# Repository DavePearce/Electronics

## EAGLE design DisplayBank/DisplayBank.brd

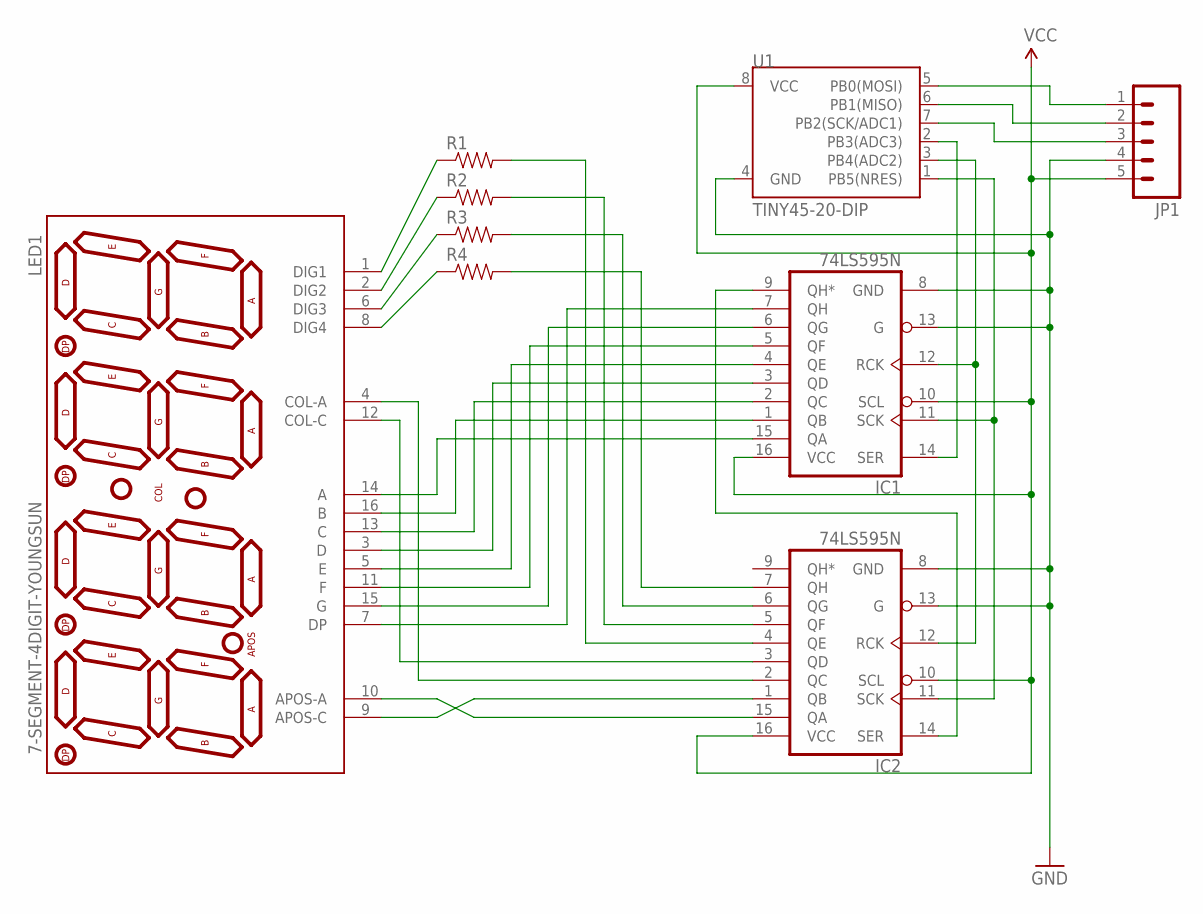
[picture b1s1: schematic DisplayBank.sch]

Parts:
IC1, IC2: 74LS595N; DIL16
JP1: M05NO_SILK; 1X05_NO_SILK
LED1: 7-SEGMENT-4DIGIT-YOUNGSUN
R1, R2, R3, R4: RESISTORPTH-1/4W; AXIAL-0.4
U1: TINY45-20-DIP; DIP08

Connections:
GND: IC1.8 (GND), IC1.13 (G), IC2.8 (GND), IC2.13 (G), JP1.4, U1.4 (GND)
unnamed: IC1.2 (QC), LED1.13 (C)
unnamed: IC1.3 (QD), LED1.3 (D)
unnamed: IC1.15 (QA), LED1.14 (A)
unnamed: IC1.1 (QB), LED1.16 (B)
unnamed: IC1.4 (QE), LED1.5 (E)
unnamed: IC1.5 (QF), LED1.11 (F)
unnamed: IC1.6 (QG), LED1.15 (G)
unnamed: IC1.7 (QH), LED1.7 (DP)
unnamed: IC1.9 (QH*), IC2.14 (SER)
unnamed: LED1.8 (DIG4), R4.P$1 (1)
unnamed: LED1.6 (DIG3), R3.P$1 (1)
unnamed: LED1.2 (DIG2), R2.P$1 (1)
unnamed: LED1.1 (DIG1), R1.P$1 (1)
unnamed: IC2.15 (QA), LED1.10 (APOS-A)
unnamed: IC2.1 (QB), LED1.9 (APOS-C)
unnamed: IC2.2 (QC), LED1.4 (COL-A)
unnamed: IC2.3 (QD), LED1.12 (COL-C)
unnamed: IC2.4 (QE), R1.P$2 (2)
unnamed: IC2.5 (QF), R2.P$2 (2)
unnamed: IC2.6 (QG), R3.P$2 (2)
unnamed: IC2.7 (QH), R4.P$2 (2)
unnamed: IC1.12 (RCK), IC2.12 (RCK), U1.3 (PB4(ADC2))
unnamed: IC1.11 (SCK), IC2.11 (SCK), U1.1 (PB5(NRES))
unnamed: JP1.1, U1.5 (PB0(MOSI))
unnamed: JP1.2, U1.6 (PB1(MISO))
unnamed: JP1.3, U1.7 (PB2(SCK/ADC1))
unnamed: IC1.14 (SER), U1.2 (PB3(ADC3))
VCC: IC1.10 (SCL), IC1.16 (VCC), IC2.10 (SCL), IC2.16 (VCC), JP1.5, U1.8 (VCC)

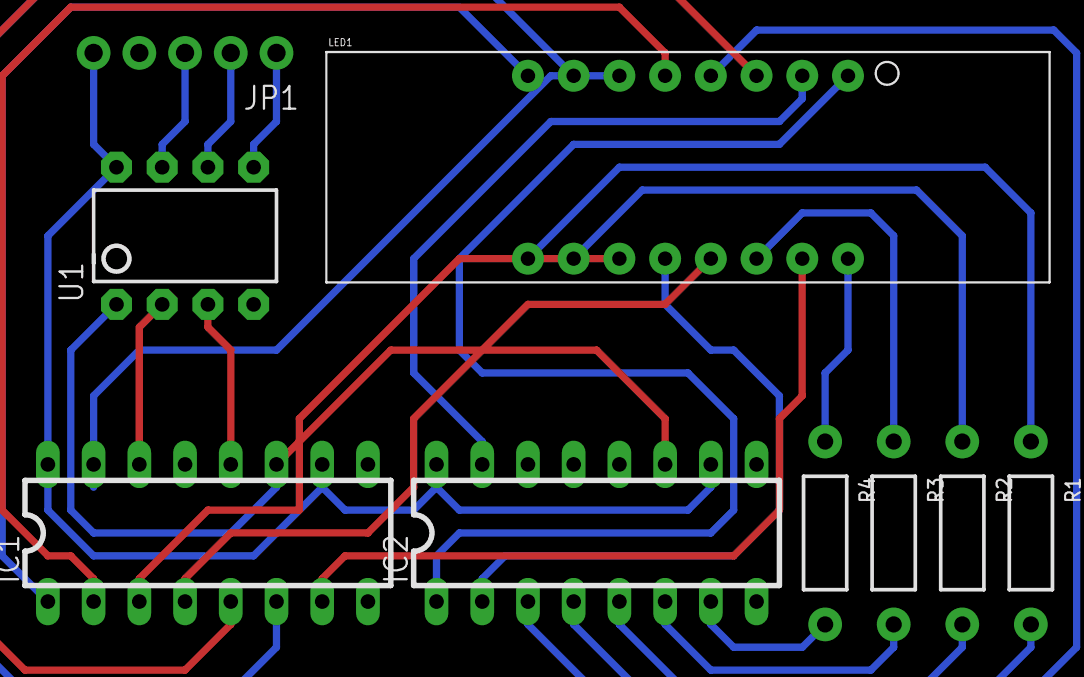
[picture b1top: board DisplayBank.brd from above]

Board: 2 copper layers, 9 parts (0 on the bottom side), 29 nets.

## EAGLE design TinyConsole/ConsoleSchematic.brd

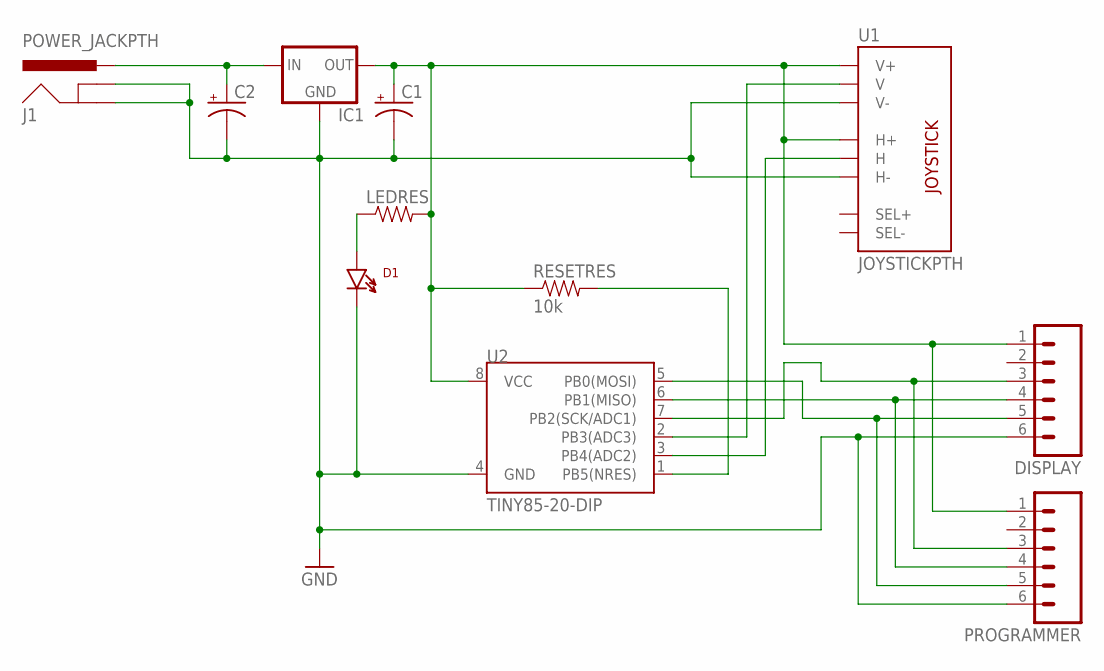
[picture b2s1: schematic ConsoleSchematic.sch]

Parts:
C1, C2: 10UF-25V-20%(PTH)KIT; CPOL-RADIAL-10UF-25V-KIT
D1: LTE-302
DISPLAY: M06SILK_FEMALE_PTH; 1X06
IC1: V_REG_78XXSIDE; 78XXL
J1: POWER_JACKPTH; POWER_JACK_PTH
LEDRES: RESISTOREZ; AXIAL-0.3EZ
PROGRAMMER: M06SILK_FEMALE_PTH; 1X06
RESETRES: 10k; AXIAL-0.3
U1: JOYSTICKPTH; JOYSTICK
U2: TINY85-20-DIP; DIP08

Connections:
CS: DISPLAY.4, PROGRAMMER.4, U2.6 (PB1(MISO))
GND: C1.2 (-), C2.2 (-), D1.C, DISPLAY.6, IC1.GND, J1.GND, J1.GNDBREAK, PROGRAMMER.6, U1.H3 (H-), U1.V3 (V-), U2.4 (GND)
MOSI: DISPLAY.5, PROGRAMMER.5, U2.5 (PB0(MOSI))
unnamed: D1.A, LEDRES.P$1 (1)
unnamed: RESETRES.P$2 (2), U2.1 (PB5(NRES))
unnamed: U1.V2 (V), U2.2 (PB3(ADC3))
unnamed: U1.H2 (H), U2.3 (PB4(ADC2))
unnamed: C2.1 (+), IC1.IN, J1.PWR
SCK: DISPLAY.3, PROGRAMMER.3, U2.7 (PB2(SCK/ADC1))
VCC: C1.1 (+), DISPLAY.1, IC1.OUT, LEDRES.P$2 (2), PROGRAMMER.1, RESETRES.P$1 (1), U1.H1 (H+), U1.V1 (V+), U2.8 (VCC)

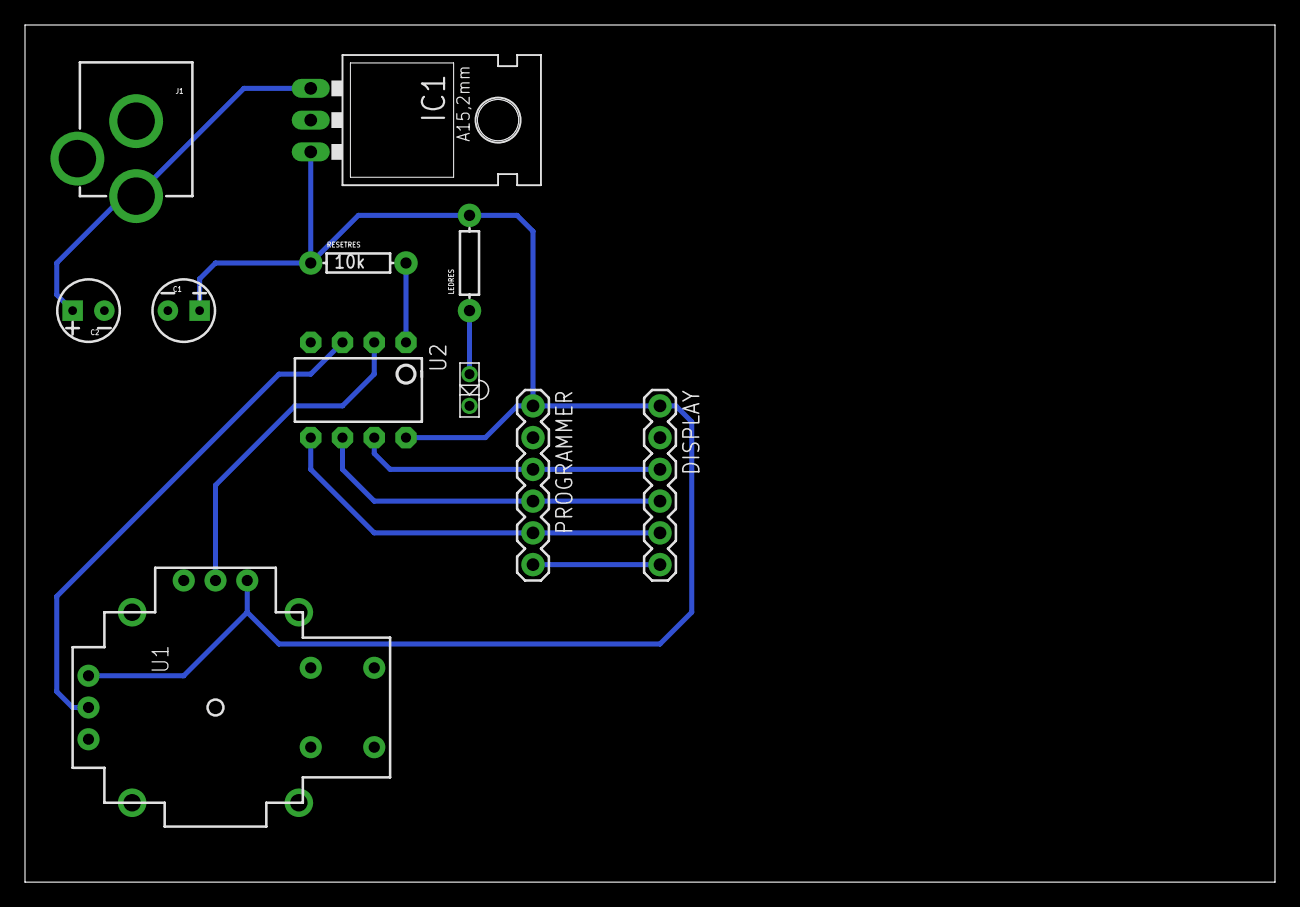
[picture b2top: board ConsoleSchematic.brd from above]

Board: 2 copper layers, 100.0 x 68.6 mm, 11 parts (0 on the bottom side), 10 nets.

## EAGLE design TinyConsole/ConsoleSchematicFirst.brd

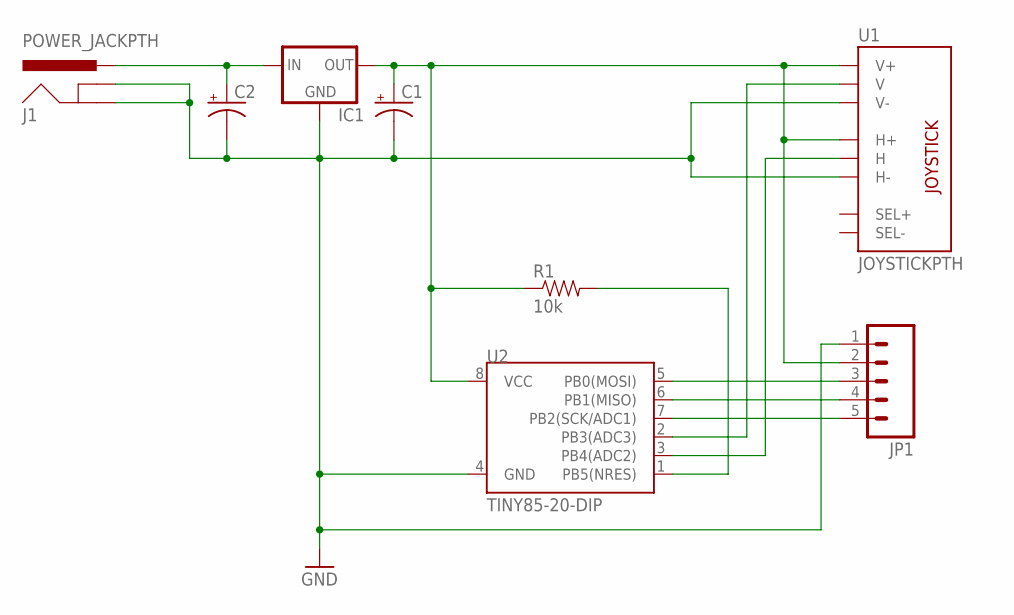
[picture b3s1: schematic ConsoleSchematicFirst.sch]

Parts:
C1, C2: 10UF-25V-20%(PTH)KIT; CPOL-RADIAL-10UF-25V-KIT
IC1: V_REG_78XXSIDE; 78XXL
J1: POWER_JACKPTH; POWER_JACK_PTH
JP1: M05LOCK; 1X05_LOCK
R1: 10k; AXIAL-0.3
U1: JOYSTICKPTH; JOYSTICK
U2: TINY85-20-DIP; DIP08

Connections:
GND: C1.2 (-), C2.2 (-), IC1.GND, J1.GND, J1.GNDBREAK, JP1.1, U1.H3 (H-), U1.V3 (V-), U2.4 (GND)
unnamed: C1.1 (+), IC1.OUT, JP1.2, R1.P$1 (1), U1.H1 (H+), U1.V1 (V+), U2.8 (VCC)
unnamed: R1.P$2 (2), U2.1 (PB5(NRES))
unnamed: U1.V2 (V), U2.2 (PB3(ADC3))
unnamed: U1.H2 (H), U2.3 (PB4(ADC2))
unnamed: JP1.5, U2.7 (PB2(SCK/ADC1))
unnamed: JP1.4, U2.6 (PB1(MISO))
unnamed: JP1.3, U2.5 (PB0(MOSI))
unnamed: C2.1 (+), IC1.IN, J1.PWR

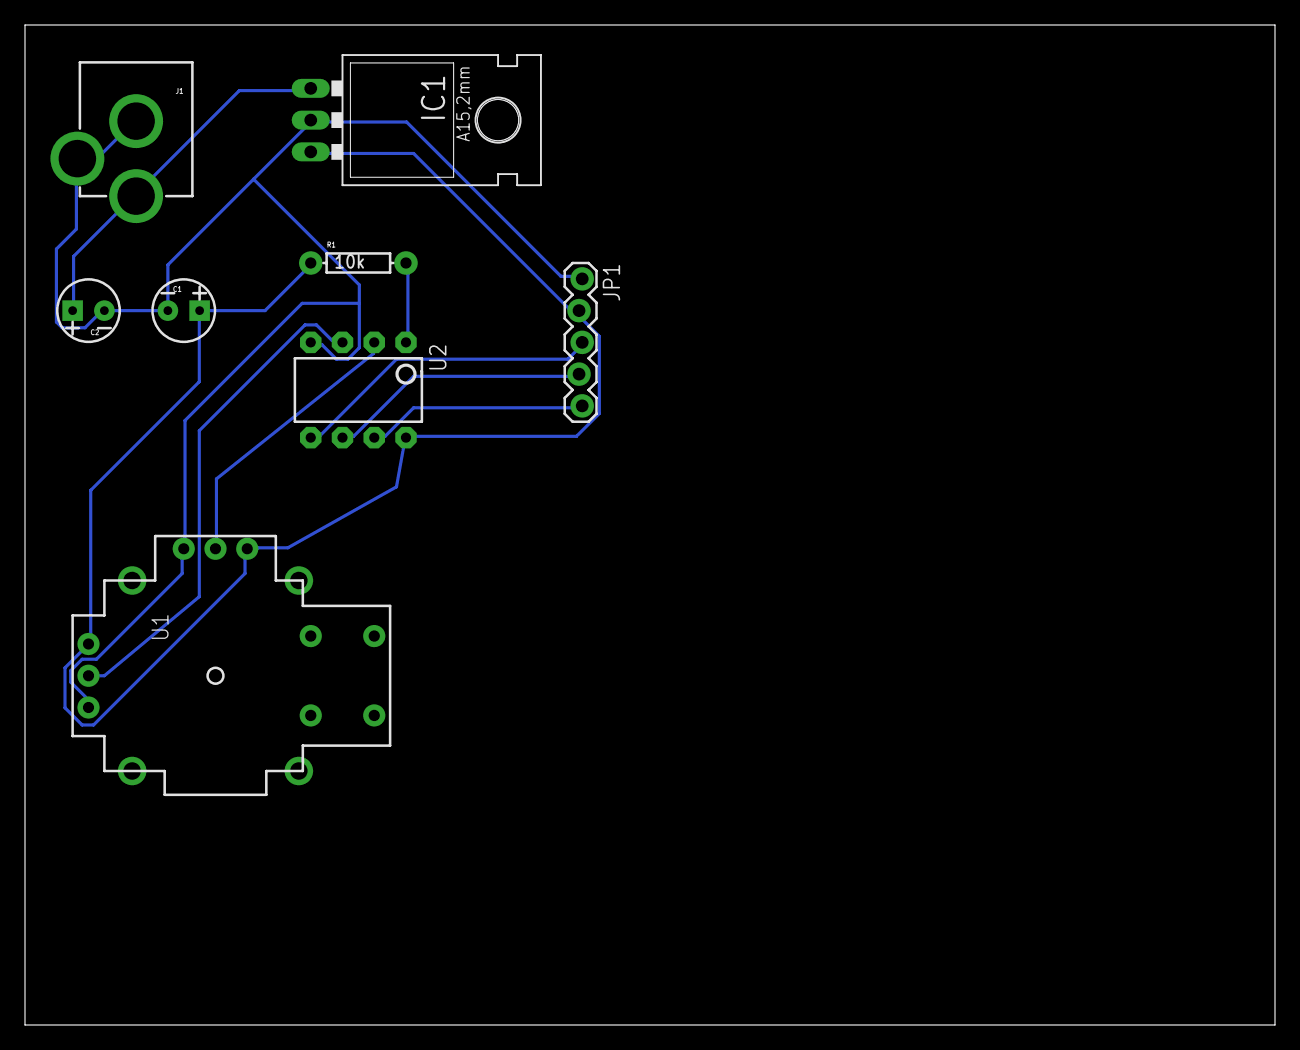
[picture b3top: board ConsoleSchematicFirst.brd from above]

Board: 2 copper layers, 100.0 x 80.0 mm, 8 parts (0 on the bottom side), 9 nets.

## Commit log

2014-11-14 Added Fritzing file for console PCB.
2014-11-14 Added Eagle files for Console.
2014-11-27 Added Autorouted Design for Console.
2014-11-27 Removed old design which was broken.
2014-11-27 Added actual files for TinyConsole.
2014-12-04 TC: Updated PCB to use Ground Plane.
    The ground plane is basically all the unused space on the PCB. Since
    the starting PCB is all copper, then we can use the ground plane as a
    continuous wire. This dramatically reduces the amount of nets needing
    to be routed.
2014-12-12 TinyConsole: Finished routing PCB.
    I've now added an LED + Resistor, along with headers for the programmer.
    I also checked the pin outs against the actual pin outs for the display
    and I believe it now lines up correctly. In short, I think it's good to
    go!!!
2015-01-11 TinyConsole: Minor tweaks before milling.
    I adjusted the dimension of the board, and reduced the amount of copper
    being filled in order to minimise problems with shorting the display.
2015-01-22 Added tetris code thus far.
2015-01-22 Added Dot Mover sketch.
2015-01-23 Updated tetris...
2015-04-17 Added DisplayBank PCB (so far)
2015-04-30 Working on the schematic
2015-04-30 Updated display PCB. Trying to figure out ground file
2015-05-01 More playing around
2015-05-01 Working on alternative routing
2015-05-01 Finished routing the display bank.
2015-05-01 Generated the gerber files.
2015-06-08 Added code for display bank.
    This code needs to be updated though to work with this.
2015-06-08 Removed broken Eagle project.
2015-06-11 Display: Adds code which runs
2015-06-11 Updated schematic
2015-06-12 DisplayBanks: Updates to PCB
2015-06-12 DisplayBank: Routing completed.
    Routing is completed now, but need to check over for errors. Also, need
    to look for opportunities to reduce space.
2015-06-18 Finished v2 of the DisplayBank.
    Version 2 of the DisplayBank fixes a number of issues I had with the
    schematic. Furthermore, it moves some of the connectors on th ATTiny85
    around so that I can program in situ. Finally, I've reduced the overall
    size of the board.
2015-07-15 Updated code for Display Mk2.
2016-01-04 Added initial code for testing USB design
    The USB design is a simple ATTiny85 connected to a USB port, along with
    a reset button. Power regulation is provided via two Zener diodes, and
    the Micronucleous USB bootloader is flashed.
    This simple example program just flashes an LED on PRB0 of the ATtiny85,
    and is installed via micronucleus.
2016-01-05 Begun SMD circuit diagram
2016-01-05 Updated SMD design; almost complete
2016-01-05 More updates
2016-01-05 Completed circuit routing, except one component
    Initial draft of circuit routing is complete. However, should really
    add the capacitor needed between +5V and GND. Also, consider whether
    can make it any smaller.
2016-01-07 Nanite85: Add Capacitor and squished design
    The design is now essentially complete, and I just need to get the
    Design Rule Checks to go through. At the moment, it's complaining that
    there are a lot of overlaps.
2016-01-10 Nanite85: Update to 603smd, and fix DRC's
    Updated to 603 sized SMD components, as those are in stock in the
    workshop. Also, went through and corrected all failing design rule
    checks. Now passes without any failures.
2016-01-11 Nanite v1.0
    This version of the USB circuit based on the Nanite85 is now ready for
    production. Fingers crossed!!
2016-01-11 Nanite85: Add G-Code
2016-01-26 Display: working on gcc-avr makefile
2016-01-26 minor
2016-12-09 Begun musical book project.
2016-12-10 Updated book projectr
2016-12-15 Version 1 of Musical Book ready for production.
2016-12-30 MusicalBook: Successful test complete
    This completes a successful test of the initial MusicalBook board.
    Although the test was successful, a fault was identified (ATMega GND not
    connected to GND). Aside from that, it appears to work well for this
    test.
    The test itself simply uploads an LED blinker, with the LED connected to
    the SPEAKER output terminal. The test doesn't check any of the input
2017-01-01 Completed page INPUT tests
    This has now tested the inputs for the first three pages. They are all
    working correctly.
2017-08-11 Add FPGA led counter example.
2017-08-11 Add SevenSegment example
2021-04-21 Simple build file for Arduino
    This puts together a simple makefile for the Arduino which can be used
    to flash it, along with avrdude.

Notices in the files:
parts and their libraries:
SparkFun-DigitalIC: Licensing: Creative Commons ShareAlike 4.0 International - https://creativecommons.org/licenses/by-sa/4.0
SparkFun-Aesthetics: Released under the Creative Commons Attribution Share-Alike 4.0 License
SparkFun-Aesthetics: https://creativecommons.org/licenses/by-sa/4.0
